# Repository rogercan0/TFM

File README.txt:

The current traces in the Traces folder are PGP encrypted and will be deleted shortly after the project's presentation due to company policies.
If you want to test the code ask for the public key at rogercano97@gmail.com

In the NVM_detection folder there are 2 files:
1) NVM_detection.ipynb: A step by step description of the developed algorithm. The default trace used as an example is 07_08.txt
2) Full_Sweep.ipynb: The automated algorithm that will generate a .png file for every current trace. The images consist on the plotted traces in blue and the detected starting point of the NVM operation in red. The output format of the names are "preDelay_postDelay_startSample". The code should be run until an error is reached, which will indicate that all of the traces have been swept. The images will be generated within the NVM_Detection folder.

Note that in order for the code to work, the Traces folder must be decrypted and unzipped.

The Hardware folder contains the KiCad project and library dependencies of the custom Sol PCB, but requires having KiCad installed in the PC to run it. The schematics and Gerber files can be visualized without the need of additional software.

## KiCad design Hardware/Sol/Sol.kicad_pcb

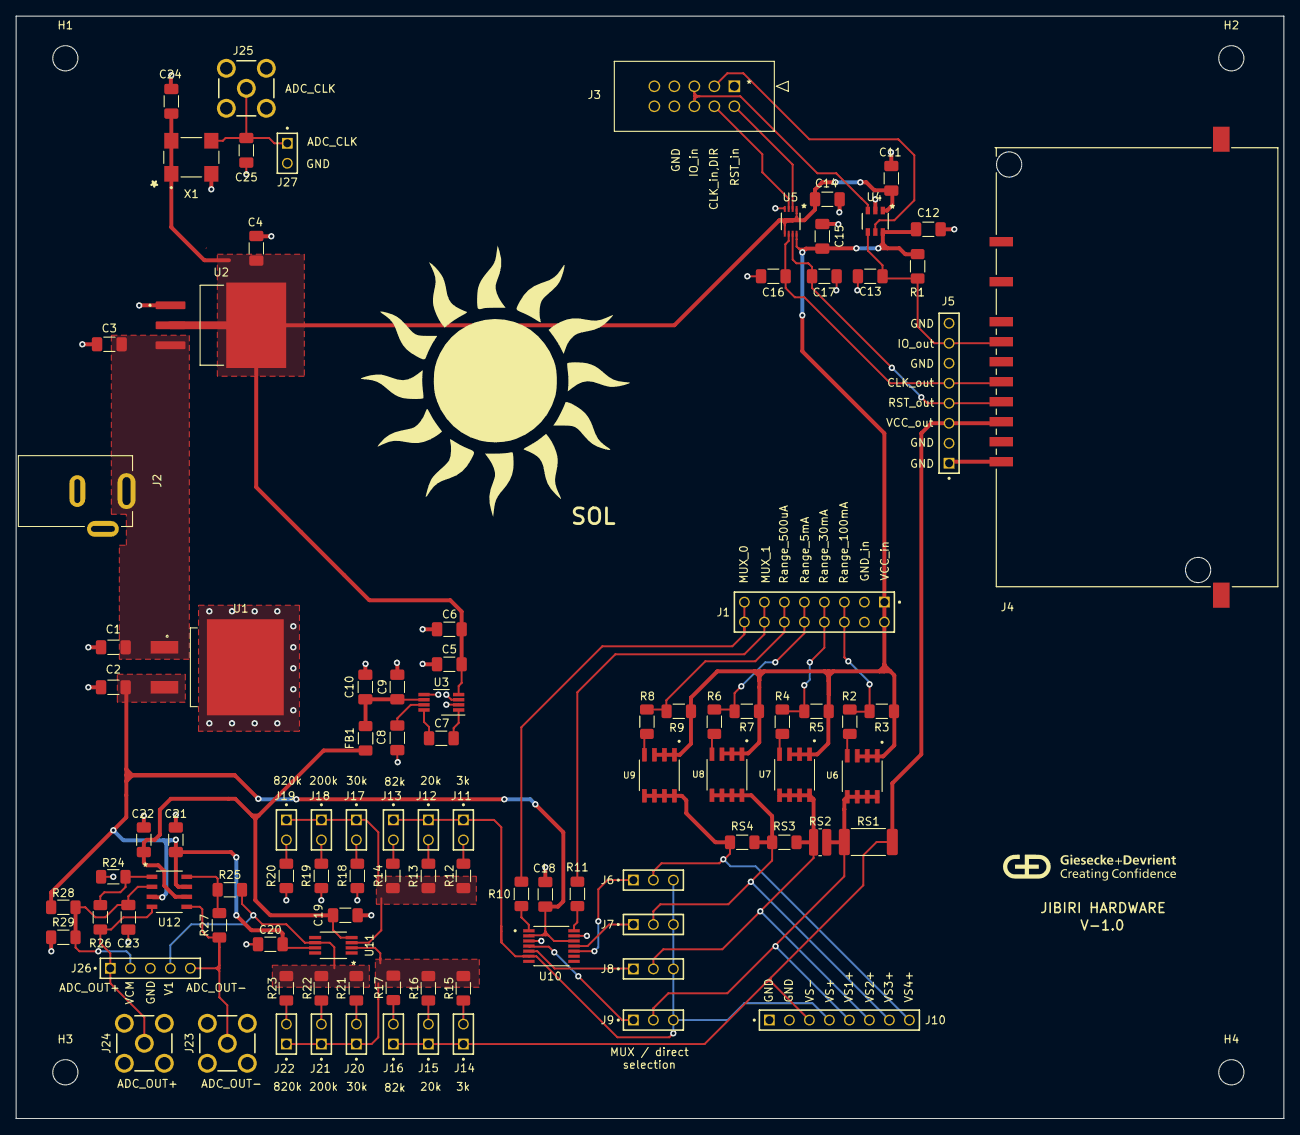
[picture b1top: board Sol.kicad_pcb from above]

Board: 2 copper layers, 161.0 x 140.0 mm, 103 parts (0 on the bottom side), 60 nets.

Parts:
C1: 0.33uF; C_1206_3216Metric_Pad1.33x1.80mm_HandSolder
C2, C6, C11, C12, C14, C15, C18, C19, C20, C21, C22, C23, C24: 0.1uF; C_1206_3216Metric_Pad1.33x1.80mm_HandSolder
C3, C4, C5: 10uF; C_1206_3216Metric_Pad1.33x1.80mm_HandSolder
C7, C8: 4.7uF; C_1206_3216Metric_Pad1.33x1.80mm_HandSolder
C9: 22uF; C_1206_3216Metric_Pad1.33x1.80mm_HandSolder
C10: 0.47uF; C_1206_3216Metric_Pad1.33x1.80mm_HandSolder
C13, C16, C17, C25: 30pF; C_1206_3216Metric_Pad1.33x1.80mm_HandSolder
FB1: 120; R_1206_3216Metric_Pad1.30x1.75mm_HandSolder
H1, H2, H3, H4: MountingHole; MountingHole_3.2mm_M3
J1: TSW-108-07-T-D
J2: RAPC722
J3: 702461001
J4: 840-2L123312001
J5, J10: TSW-108-07-T-S
J6, J7, J8, J9: TSW-103-07-T-S
J11, J12, J13, J14, J15, J16, J17, J18, J19, J20, J21, J22, J27: TSW-102-07-T-S
J23, J24, J25: SMA-J-P-H-ST-TH1
J26: TSW-105-07-T-S
R1, R13, R16, R29: 20k; R_1206_3216Metric_Pad1.30x1.75mm_HandSolder
R2, R4, R6, R8, R12, R15: 3k; R_1206_3216Metric_Pad1.30x1.75mm_HandSolder
R3, R5, R7, R9: 10k; R_1206_3216Metric_Pad1.30x1.75mm_HandSolder
R10, R11: 1k; R_1206_3216Metric_Pad1.30x1.75mm_HandSolder
R14, R17: 82k; R_1206_3216Metric_Pad1.30x1.75mm_HandSolder
R18, R21: 30k; R_1206_3216Metric_Pad1.30x1.75mm_HandSolder
R19, R22: 200k; R_1206_3216Metric_Pad1.30x1.75mm_HandSolder
R20, R23: 820k; R_1206_3216Metric_Pad1.30x1.75mm_HandSolder
R24, R25: 348; R_1206_3216Metric_Pad1.30x1.75mm_HandSolder
R26, R27: 2k; R_1206_3216Metric_Pad1.30x1.75mm_HandSolder
R28: 178k; R_1206_3216Metric_Pad1.30x1.75mm_HandSolder
RS1: 0.3; R_2512_6332Metric_Pad1.40x3.35mm_HandSolder
RS2: 0.75; R_0612_1632Metric_Pad1.18x3.40mm_HandSolder
RS3: 5.1; R_1206_3216Metric_Pad1.30x1.75mm_HandSolder
RS4: 56; R_1206_3216Metric_Pad1.30x1.75mm_HandSolder
U1: L7809; L7809ABD2T-TR
U2: LM1084-3.3; LM1084IS-3.3_NOPB
U3: LM7705; VSSOP-8_3.0x3.0mm_P0.65mm
U4: SN74LXC1T45DBVR; 74XXX1T45
U5: SN74LXC2T45DCUR; 74XXX2T45
U6, U7, U8, U9: SI4421DY-T1-E3
U10: ADG1404YRUZ
U11: OPA189IDGKT; OPA189DKGT
U12: THP210DR
X1: CB3LV-5I-10M0000

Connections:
+3.3V: C4.1, C5.1, C6.1, C11.1, C14.1, C24.2, U2.2 (VO), U3.4 (VDD), U4.1 (VCCA), U5.1 (VCCA), U5.5 (DIR), X1.1 (EOH), X1.4 (VCC)
+9V: C2.2, C18.2, C20.2, C21.2, R28.1, U1.3 (OUT), U10.2 (EN), U10.12 (VDD), U11.7 (V+), U12.3 (VS+), U12.7 (PG)
+12V: C1.2, C3.1, J2.PIN, U1.1 (IN), U2.3 (VI)
-0.232V: C19.2, C22.1, FB1.2, U11.4 (V-), U12.6 (VS-)
/AFE/V1: J26.04, R21.2, R22.2, R23.2, R25.1, U11.6 (OUT)
/AFE/VCM: C23.2, J26.02, R28.2, R29.1, U12.2 (VOCM)
/AFE/VFB+: J17.01, J18.01, J19.01, R12.2, R13.2, R14.2, U11.3 ('+IN)
/AFE/VFB_IN-: J20.01, J21.01, J22.01, R15.2, R16.2, R17.2, U11.2 ('-IN)
/Kraken/CLK_in: J3.4, U5.3 (A2)
/Kraken/CLK_out: C16.1, J4.C3, J5.05, U5.6 (B2)
/Kraken/DIR: J3.3, U4.5 (DIR)
/Kraken/IO_in: J3.5, J3.6, U4.3 (A)
/Kraken/IO_out: C13.1, J4.C7, J5.07, R1.2, U4.4 (B)
/Kraken/RST_in: J3.2, U5.2 (A1)
/Kraken/RST_out: C17.1, J4.C2, J5.04, U5.7 (B1)
/Ranges/VMUX1: J9.01, U10.4 (S1)
/Ranges/VMUX2: J8.01, U10.5 (S2)
/Ranges/VMUX3: J7.01, U10.11 (S3)
/Ranges/VMUX4: J6.01, U10.10 (S4)
/Ranges/VS1+: J9.02, J10.05, RS1.1, RS2.2, U6.5, U6.6, U6.7, U6.8
/Ranges/VS2+: J8.02, J10.06, RS2.1, RS3.2, U7.5, U7.6, U7.7, U7.8
/Ranges/VS3+: J7.02, J10.07, RS3.1, RS4.2, U8.5, U8.6, U8.7, U8.8
/Ranges/VS4+: J6.02, J10.08, RS4.1, U9.5, U9.6, U9.7, U9.8
ADC_CLK: C25.2, J25.1, J27.01, X1.3 (OUT)
ADC_IN+: J24.1, J26.01, R26.2, U12.4 (OUT+)
ADC_IN-: J23.1, J26.05, R27.2, U12.5 (OUT-)
GND: C1.1, C2.1, C3.2, C4.2, C5.2, C6.2, C8.2, C9.2, C10.2, C11.2, C12.2, C13.2, C14.2, C15.2, C16.2, C17.2, C18.1, C19.1, C20.1, C21.1, C22.2, C23.1, C24.1, C25.1, J1.03, J1.04, J2.SHUNT, J2.SLEEVE, J3.7, J3.8, J4.C5, J5.01, J5.02, J5.06, J5.08, J10.01, J10.02, J23.2, J23.3, J23.4, J23.5, J24.2, J24.3, J24.4, J24.5, J25.2, J25.3, J25.4, J25.5, J26.03, J27.02, R18.2, R19.2, R20.2, R24.1, R29.2, U1.2 (GND), U2.1 (GND), U3.2 (GND), U3.3 (SD), U3.5 (GND), U4.2 (GND), U5.4 (GND), U10.3 (VSS), U10.13 (GND), X1.2 (GND)
MUX_0: J1.15, J1.16, R10.1
MUX_1: J1.13, J1.14, R11.1
unnamed: J11.02, R12.1
unnamed: J12.02, R13.1
unnamed: J13.02, R14.1
unnamed: J14.02, R15.1
unnamed: J15.02, R16.1
unnamed: J16.02, R17.1
unnamed: J17.02, R18.1
unnamed: J18.02, R19.1
unnamed: J19.02, R20.1
unnamed: J20.02, R21.1
unnamed: J21.02, R22.1
unnamed: J22.02, R23.1
unnamed: R2.1, U6.4
unnamed: R4.1, U7.4
unnamed: R6.1, U8.4
unnamed: R8.1, U9.4
unnamed: C7.1, U3.1 (CF+)
unnamed: C7.2, U3.8 (CF-)
unnamed: C8.1, U3.7 (CRES)
unnamed: C9.1, C10.1, FB1.1, U3.6 (VOUT)
unnamed: R10.2, U10.1 (A0)
unnamed: R11.2, U10.14 (A1)
unnamed: R25.2, R27.1, U12.8 (IN+)
unnamed: R24.2, R26.1, U12.1 (IN-)
Range_5mA: J1.09, J1.10, R6.2, R7.2
Range_30mA: J1.07, J1.08, R4.2, R5.2
Range_100mA: J1.05, J1.06, R2.2, R3.2
Range_500uA: J1.11, J1.12, R8.2, R9.2
VCC_in: C12.1, C15.1, J1.01, J1.02, R1.1, R3.1, R5.1, R7.1, R9.1, U4.6 (VCCB), U5.8 (VCCB), U6.1, U6.2, U6.3, U7.1, U7.2, U7.3, U8.1, U8.2, U8.3, U9.1, U9.2, U9.3
VCC_out: J4.C1, J5.03, J10.03, J14.01, J15.01, J16.01, RS1.2
VS+: J6.03, J7.03, J8.03, J9.03, J10.04, J11.01, J12.01, J13.01, U10.6 (D)

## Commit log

2024-09-10 Full commit
2024-09-10 Adding the Results folder.
2024-09-10 More info in the README
2024-09-12 Encrypted and compressed the current traces.
